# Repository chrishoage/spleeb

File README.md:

# Spleeb

Another split keyboard... a "Spleeb".

This split keyboard is created using [Ergogen](https://github.com/ergogen/ergogen/) and the routing done manually, copied back into the yaml file. This was inspired a lot by the Ergodash which I used for about a year but wanted something that fit my use and hands a bit better.

## ‼ NOTE ‼

Photos are pictured with heat set inserts in the bottom chassis that **_ARE NOT_** present in the STEP or Fusion 360 files. I was not happy with how the approach I took worked, and didn't want to release something that people may actually use (like the original touchpad bracket which was particularly poorly designed). I didn't want to reprint the bottom just to take some photos. The models in this repo are exactly the same, I just removed the holes for the heat set inserts on the side.

You can read more about the [Spleeb Chassis 1.2 revision in the Pull Request which added it](https://github.com/chrishoage/spleeb/pull/5).

### Features

- Reversible PCB
- Optional rotary encoder replacing the bottom left key switch
- OLED screen covering the MCU on the inside of the board
- No acrylic case, only 3D printed case and plate, or cut plate
- No RGB (a joke - I don't use LEDs on keyboards but am open to accepting PRs if someone wants to do the work)

| Left                                         | Right                                          |
| -------------------------------------------- | ---------------------------------------------- |
|  |  |
|           |           |

### Motivation

I'm not a fan of excessive layers, and many of the popular split keyboards are 3x5 and make heavy use of layers. I used the Ergodash for a while but found the placement of the mods to be uncomfortable, and the top row of the thumb cluster to be unused. Seeing some keyboards (like the [bastard keyboards' dilemma](https://bastardkb.com/dilemma/)) which leveraged the Cirque touchpad inspired me to create my own keyboard which allowed for the layout I wanted, along with all the bells and whistles like rotary encoders, oled screen and touchpad. A secondary purpose of this was to learn Fusion 360, KiCad, and a teensy tiny bit of C and electrical engineering.

### BOM

| Item                                              | Quantity | Notes                                                                                                                                                                    |
| ------------------------------------------------- | -------- | ------------------------------------------------------------------------------------------------------------------------------------------------------------------------ |
| Spleeb PCB                                        | 2        |                                                                                                                                                                          |
| Spleeb Plate                                      | 2        | Intended to be cut from FR4 during PCB fab but this can be 3D printed. Extrude the plate dxf to 1.5mm and it will be 3d printable (fit accuracy depends on your printer) |
| Cirque 35mm Touchpad Flat overlay TM035035        | 1        | i2c only. The SPI version can be modified to use i2c.                                                                                                                    |
| SSD1306 128x64 OLED                               | 1        | DIYmall model and footprint used in chassis model. Other brands may have fit issues with out modification of the model.                                                  |
| Pro Micro pin MCU                                 | 2        | RP2040 recomended. Boardsource Blok used in build                                                                                                                        |
| MX switches                                       | 62       |                                                                                                                                                                          |
| 1u keycaps                                        | 58       |                                                                                                                                                                          |
| 1.25u keycaps                                     | 4        |                                                                                                                                                                          |
| EC11 Encoder                                      | 2        | Alps Alpine EC11N1524402 used in build                                                                                                                                   |
| Encoder Kob                                       | 2        | 18mm diameter                                                                                                                                                            |
| 1N4148 Through Hole Diodes                        | 64       | SMD diodes supported on PCB but this has not been tested                                                                                                                 |
| PJ-320A 3.5 mm jack                               | 2        |                                                                                                                                                                          |
| Alps Alpine SKHLLCA010                            | 2        | Reset Switch                                                                                                                                                             |
| JST PH 2.0 mm 4 pin straight connector            | 2        | These are optional. Wires can be soldered directly to the though hole pads on the PCB. The connectors make disassembly easier.                                           |
| Mill-Max 315-93 Low Profile Sockets               | 48       | These are optional. However the height of regular headers is slightly higher than these, so may need adjusting to the USB cutout                                         |
| Mill-Max 3320 Socket Pins                         | 48       | These are optional. These are for the Mill-Max sockets                                                                                                                   |
| Mill-Max 3305-1 Switch Sockets                    | 124      | These are optional. These allow switches to be swapped with out resoldering                                                                                              |
| M3 M3x5x4 threaded heat set inserts               | 8        | Used to fasten bottom to top of chassis. (Same as the Voron 2.4/Trident BOM)                                                                                             |
| M3 12mm length socket head screws                 | 8        | Used to fasten bottom to top of chassis. 10mm _should_ work as well.                                                                                                     |
| M2 4mm installed length threaded heat set inserts | 10       | Used to fasten plate to top and Cirque bracket to top. Up to 20 may be used depending on how much stiffness in the plate is desired.                                     |
| M2 8mm length ultra low profile screws            | 8        | Used to attach plate to top. Minimum 8. Up to 20 may be used depending on how many M2 heat set inserts are installed top top.                                            |
| Silicone O-Rings, 4mm OD 1mm ID 1.5mm Width       | 16       | Used for a poor man's burger mount isolation for the plate and top                                                                                                       |
| M2 4mm length ultra low profile screws            | 6        | 2-4 for the oled, 2 for the angled Ciruqe bracket                                                                                                                        |
| Hookup Wire                                       | x        | Needed for OLED and Cirque Touchpad                                                                                                                                      |

### Build Notes (Spleeb Chassis rev 1.2)

Most of this build is straight forward and would follow any PCB build. Look for the diode silkscreen to know which direction didoes should go.

The original chassis CAD files created using Fusion 360 [are included](./chassis/) and the step files for all parts included as well.

There are [more photos](/images/) not shown in the readme in th images directory.

#### "Burger" Mount

Two silicone O-rings are to be placed in-between the plate and the contact points. One under the screw head and one under the plate. The plate is then screwed into the "top" of the chassis for a top mount approach.

The original plate had 10 attachment points for the "sandwich" mount chassis that was designed before this current iteration. In hindsight this was far too many. While the design and 3d models still support all 10 attachment points, only 4 need to be used.

I am currently using the two on each side of the plate and it feels just fine and there is no rattle. Tightening down the screws all the way is not necessary, just enough so that the plate doesn't move.

|                                                                        |                                                                                           |
| ---------------------------------------------------------------------- | ----------------------------------------------------------------------------------------- |
|  |  |

#### MCU Mounting and MCU Solder pads

This PCB has solder pads on each side of the PCB. These solder pads allow the MCU to be mounted on either side of the PCB - however the intended use for this build is mounting the MCUs on the _underside_ of the PCB - the side opposite the switches, with the MCU LED facing up. With this orientation the solder pads should be solder on the \*same side as the switches.

The solder pad opposite the through hole pad marked with the square 🔳 is RAW.

If you mount the MCU with the LED facing out on the top (same side as switches) you would solder the pads on the top.

If you mount the MCU with the LED facing out on the bottom (opposite side of switches) you would solder the pads on the bottom.

If you mount the MCU with the LED facing in on the top (same side as switches) you would solder the pads on the bottom.

If you mount the MCU with the LED facing in on the bottom (opposite side of switches) you would solder the pads on the top.

Again - with the chassis as designed the last mounting option is the only one supported:

Mount the MCU on the opposite side of the switches, with the LED facing in. Solder the pads on the same side as the switches.

| MCU Orientation                                                            | Solder pads on top                                                                        |
| -------------------------------------------------------------------------- | ----------------------------------------------------------------------------------------- |
|  |  |

Since the PCB is reversible you would mirror this on the other side.

#### Cirque 35mm Touchpad

Use hookup wire to solder to the GND, VCC, SDA, SCL pads, and remove the R1 resistor if the SPI version was purchased.

#### JST PH 2.0 connector

Wires should be hooked up to connector from the "outside" edge of the pcb to "inside" (PCB is reversible)

1. SCL ("outside" - white)
1. SDA (yellow)
1. VCC (red)
1. GND ("inside" - black)

#### Cirque Touchpad Bracket

The bracket is split into three parts.

- _Support_: 35mm Cirque touchpad sits in the support. The support has indexing features to hold the touchpad in the correct orientation. The "L" embossed in the support is a rudimentary X/Y plane to remember orientation.
- _Bezel_: The Support snaps into place inside the bezel.
- _Bracket_: The Support + Bezel assembly snaps on top of the bracket which holds the assembly at a 15° angle.

|                                                                                      |                                                                                  |
| ------------------------------------------------------------------------------------ | -------------------------------------------------------------------------------- |
|       |                 |
|           |  |
|  |                  |

#### OLED attachment

The intent is that the 4mm ultra low profile screws should fasten directly into the plastic.

### Printing

I used ASA but anything should work depending on your printer. I didn't use supports for the 3.5mm and USB cutouts. YMMV on needing supports, but I designed the model to be printed with out supports.

#### Critical print parameters

There are features in this model which demand a 0.4 nozzle and 0.2mm layer hight. All other printing parameters are to taste.

### Firmware

Firmware is QMK based and [can be found in the QMK GitHub repo](https://github.com/qmk/qmk_firmware/tree/master/keyboards/spleeb).

My personal keymap customizations [can be found my my QMK Userspace Fork](https://github.com/chrishoage/qmk_userspace/tree/main/keyboards/spleeb/keymaps/chrishoage)

## License

- All code in this repository is licensed under the [MIT](./LICENSE) license.
- All images in this repository are licensed under the [Creative Commons Attribution-NonCommercial](https://creativecommons.org/licenses/by-nc/4.0/) license.
- All CAD files in this repository are licensed under the [Creative Commons Attribution-NonCommercial-ShareAlike](https://creativecommons.org/licenses/by-nc-sa/4.0/) license.

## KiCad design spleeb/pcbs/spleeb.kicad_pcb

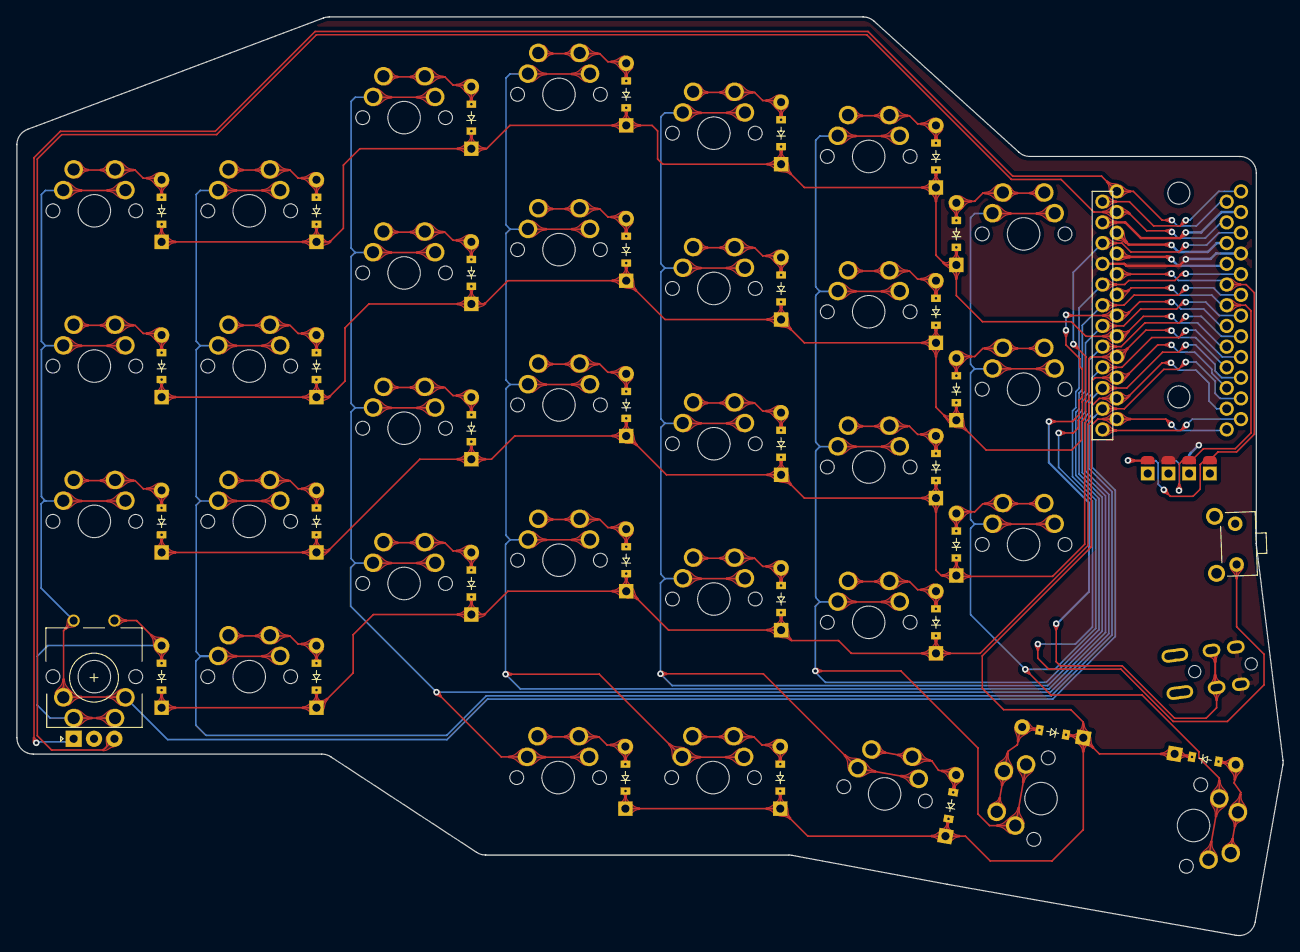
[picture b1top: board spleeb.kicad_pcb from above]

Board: 2 copper layers, 155.3 x 112.7 mm, 71 parts (1 on the bottom side), 52 nets.

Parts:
B1: SW_SKHLLCA010
D1, D2, D3, D4, D5, D6, D7, D8, D9, D10, D11, D12, D13, D14, D15, D16, D17, D18, D19, D20, D21, D22, D23, D24, D25, D26, D27, D28, D29, D30, D31, D32: ComboDiode
MCU1: ProMicro
MP1, MP2: Hole
OLED1: OLED-double-sided; OLED-128x32-double-sided
ROT1: rotary_encoder
S1, S2, S3, S4, S5, S6, S7, S8, S9, S10, S11, S12, S13, S14, S15, S16, S17, S18, S19, S20, S21, S22, S23, S24, S25, S26, S27, S28, S29, S30, S31, S32: MX
TRRS1: TRRS-PJ-320A-dual

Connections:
GND: B1.2, MCU1.2, MCU1.15, MCU1.16, OLED1.4, ROT1.C, TRRS1.1, TRRS1.2
P0: MCU1.14, ROT1.B
P1: MCU1.13, ROT1.A
P2: MCU1.17, OLED1.1
P3: MCU1.18, OLED1.2
P4: MCU1.19, TRRS1.3
P5: D4.1, D4.2, D8.1, D8.2, D12.1, D12.2, D16.1, D16.2, D20.1, D20.2, D24.1, D24.2, D27.1, D27.2, MCU1.20
P6: D3.1, D3.2, D7.1, D7.2, D11.1, D11.2, D15.1, D15.2, D19.1, D19.2, D23.1, D23.2, D26.1, D26.2, MCU1.21
P7: D2.1, D2.2, D6.1, D6.2, D10.1, D10.2, D14.1, D14.2, D18.1, D18.2, D22.1, D22.2, D25.1, D25.2, MCU1.22
P8: D1.1, D1.2, D5.1, D5.2, D9.1, D9.2, D13.1, D13.2, D17.1, D17.2, D21.1, D21.2, MCU1.23
P9: D28.1, D28.2, D29.1, D29.2, D30.1, D30.2, D31.1, D31.2, D32.1, D32.2, MCU1.24
P14: MCU1.10, S5.2, S6.2, S7.2, S8.2
P15: MCU1.9, S9.2, S10.2, S11.2, S12.2, S28.2
P16: MCU1.11, ROT1.1, S1.2, S2.2, S3.2, S4.2
P18: MCU1.8, S13.2, S14.2, S15.2, S16.2, S29.2
P19: MCU1.7, S17.2, S18.2, S19.2, S20.2, S30.2
P20: MCU1.6, S21.2, S22.2, S23.2, S24.2, S31.2
P21: MCU1.5, S25.2, S26.2, S27.2, S32.2
RST: B1.1, MCU1.3
VCC: MCU1.4, OLED1.3, TRRS1.4
extra_home: D25.1, D25.2, S25.1
extra_number: D27.1, D27.2, S27.1
extra_top: D26.1, D26.2, S26.1
far_mods: D32.1, D32.2, S32.1
home_mods: D31.1, D31.2, S31.1
index_bottom: D17.1, D17.2, S17.1
index_home: D18.1, D18.2, S18.1
index_number: D20.1, D20.2, S20.1
index_top: D19.1, D19.2, S19.1
inner_bottom: D21.1, D21.2, S21.1
inner_home: D22.1, D22.2, S22.1
inner_number: D24.1, D24.2, S24.1
inner_top: D23.1, D23.2, S23.1
middle_bottom: D13.1, D13.2, S13.1
middle_home: D14.1, D14.2, S14.1
middle_number: D16.1, D16.2, S16.1
middle_top: D15.1, D15.2, S15.1
mod_one_mods: D28.1, D28.2, S28.1
mod_two_mods: D29.1, D29.2, S29.1
near_mods: D30.1, D30.2, S30.1
outer_bottom: D1.1, D1.2, ROT1.2, S1.1
outer_home: D2.1, D2.2, S2.1
outer_number: D4.1, D4.2, S4.1
outer_top: D3.1, D3.2, S3.1
pinky_bottom: D5.1, D5.2, S5.1
pinky_home: D6.1, D6.2, S6.1
pinky_number: D8.1, D8.2, S8.1
pinky_top: D7.1, D7.2, S7.1
ring_bottom: D9.1, D9.2, S9.1
ring_home: D10.1, D10.2, S10.1
ring_number: D12.1, D12.2, S12.1
ring_top: D11.1, D11.2, S11.1

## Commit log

2022-08-09 Initial spleebing
2022-08-10 Address DRC errors with GND
2022-08-10 Make preview a dev only outline
2022-08-11 dont track kicad backups
2022-08-12 Replace jumper pad promicro footprint with reversable thru hole footprint to allow standoffs for oled
2022-08-13 Updates for plate including oled cutout
2022-08-14 use absoluteOutputPath for clean command
2022-08-14 load teardrop plugin and run with defaults before fill
2022-08-14 move from docker to pipx for now and use fixed pcbdraw along with clean
2022-08-14 use pipx instead of docker for kikit
2022-08-14 address issues after 3d model test and build with new build changes
2022-08-27 remove oled mounting posts and replate with jstph. move rot enc, trrs and rst btn
2022-08-27 back to reversable jumper footprint
2022-09-01 move trrs, rest, and mcu
2022-09-02 add pcb artwork
2022-09-02 fix jstph plate cutout location
2022-09-06 final adjustments to plate
2022-09-06 regenerate files
2022-12-31 add step and fusion files for case
2023-01-01 fill out readme and add images
2023-01-01 more readme edits
2023-01-02 add licenses and small readme fixes
2023-01-02 It has been fabricated
2023-03-21 Add link to firmware in readme
2023-04-03 Add sockets to BOM and add MCU Mouting and solder pad instructions
2023-04-25 Add mising reset switch to BOM
2023-05-03 Add visual example of correct MCU and pad solder position
2024-08-26 Add Spleeb Chassis 1.2 Revision models, images, and README updates
